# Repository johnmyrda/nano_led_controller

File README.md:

# nano_led_controller
Eagle PCB Files for LED controller used in my [multi-beacon](https://github.com/johnmyrda/multi-beacon) project.

I created this PCB to make it easier to fit an Arduino Nano inside a [RadioShack 3x2x1 Project Box](https://www.radioshack.com/products/radioshack-project-enclosure-3x2x1).

TODO: Add BOM

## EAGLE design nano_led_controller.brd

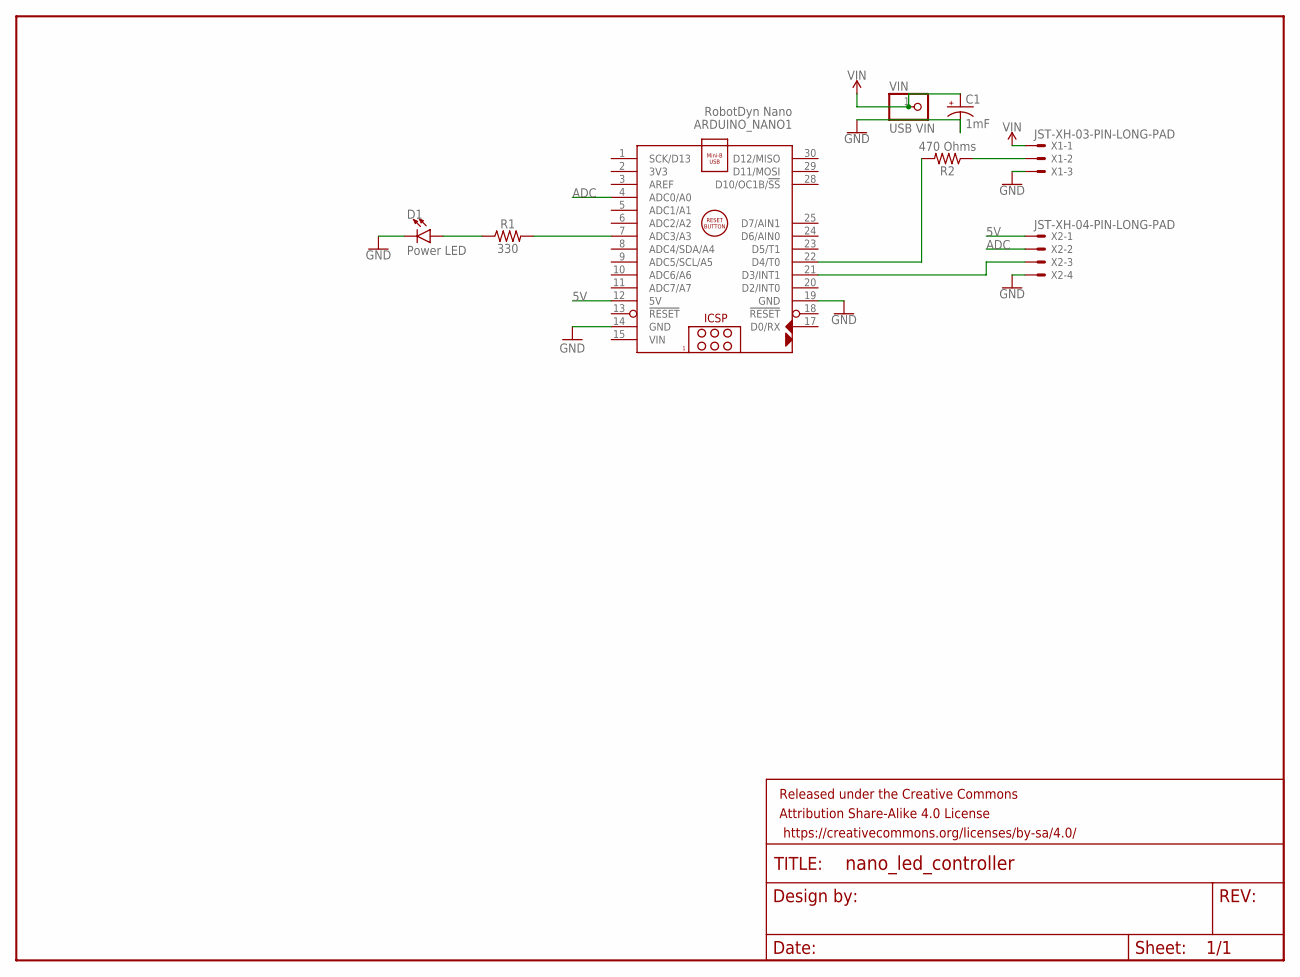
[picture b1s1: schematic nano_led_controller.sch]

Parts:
ARDUINO_NANO1: RobotDyn Nano; ARDUINO_NANO
C1: 1mF; CPOL-RADIAL-5MM-10MM
D1: Power LED; LED_3MM-NS
FRAME1: FRAME-LETTER; CREATIVE_COMMONS
R1: 330; AXIAL-0.3
R2: 470 Ohms; AXIAL-0.3
VIN: USB VIN; 1X01
X1: JST-XH-03-PIN-LONG-PAD; JST-XH-03-PACKAGE-LONG-PAD
X2: JST-XH-04-PIN-LONG-PAD; JST-XH-04-PACKAGE-LONG-PAD

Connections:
5V: ARDUINO_NANO1.12 (5V), X2.1
ADC: ARDUINO_NANO1.4 (ADC0/A0), X2.2
GND: ARDUINO_NANO1.14 (GND), ARDUINO_NANO1.19 (GND), C1.-, D1.K (C), X1.3, X2.4
unnamed: ARDUINO_NANO1.7 (ADC3/A3), R1.P$2 (2)
unnamed: R2.P$1 (1), X1.2
unnamed: ARDUINO_NANO1.22 (D4/T0), R2.P$2 (2)
unnamed: D1.A, R1.P$1 (1)
unnamed: ARDUINO_NANO1.21 (D3/INT1), X2.3
VIN: ARDUINO_NANO1.15 (VIN), C1.+, VIN.1, X1.1

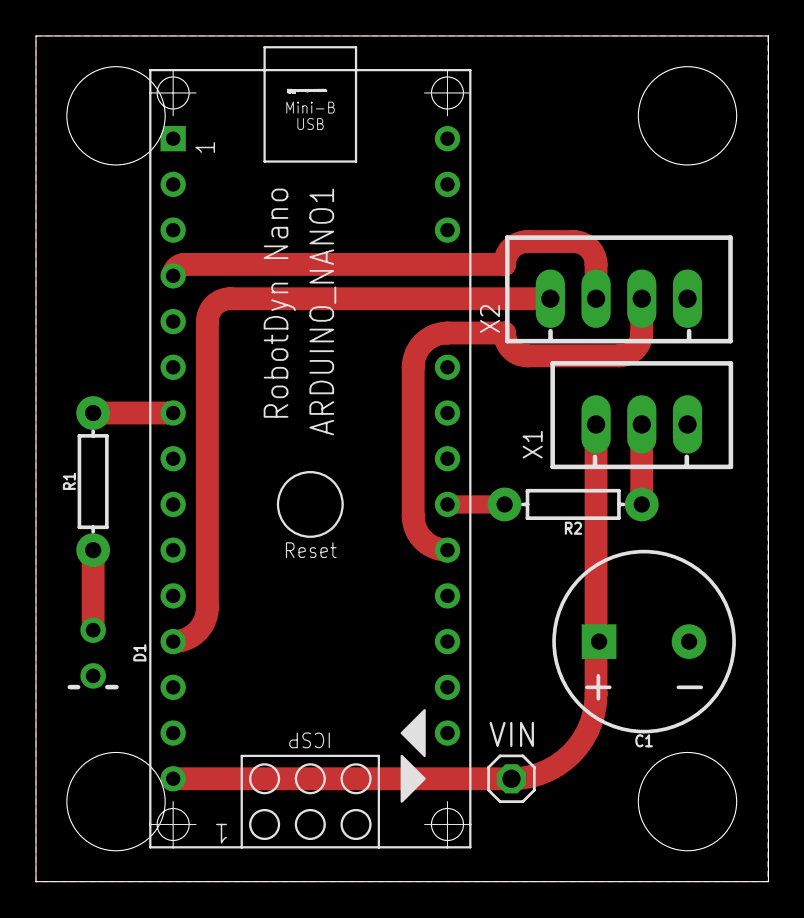
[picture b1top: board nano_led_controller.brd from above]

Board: 2 copper layers, 40.7 x 47.0 mm, 9 parts (0 on the bottom side), 9 nets.

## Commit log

2017-06-01 Initial Controller board and schematic
2017-06-01 Rearranged board to work with right angle USB cable
2017-06-01 50mil traces and more ground plane Pins 16(D1/TX),26(D8/CLK0),27(D9/OC1A) are out of commission.
2017-06-11 Removed some unused pins to simplify routing

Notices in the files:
parts and their libraries:
SparkFun-Capacitors: Licensing: Creative Commons ShareAlike 4.0 International - https://creativecommons.org/licenses/by-sa/4.0
SparkFun-Aesthetics: Released under the Creative Commons Attribution Share-Alike 4.0 License
SparkFun-Aesthetics: https://creativecommons.org/licenses/by-sa/4.0
